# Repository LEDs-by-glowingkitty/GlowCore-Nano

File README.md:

# GlowCore-Nano
The tiniest GlowCore ever! With all the core features you need to make LEDs glow.

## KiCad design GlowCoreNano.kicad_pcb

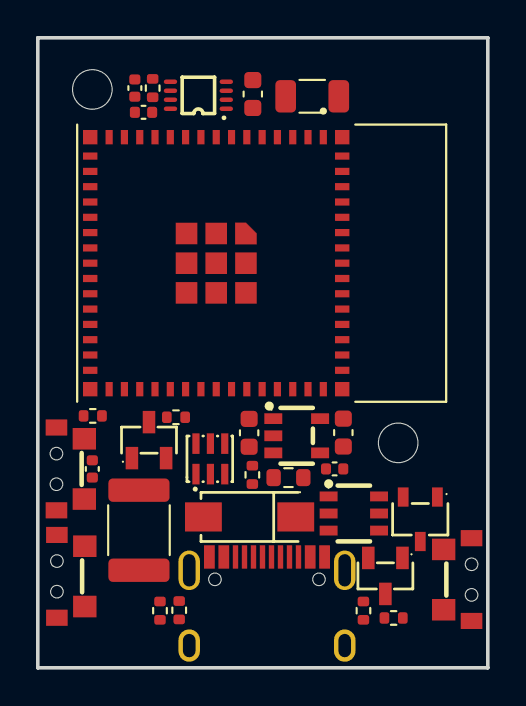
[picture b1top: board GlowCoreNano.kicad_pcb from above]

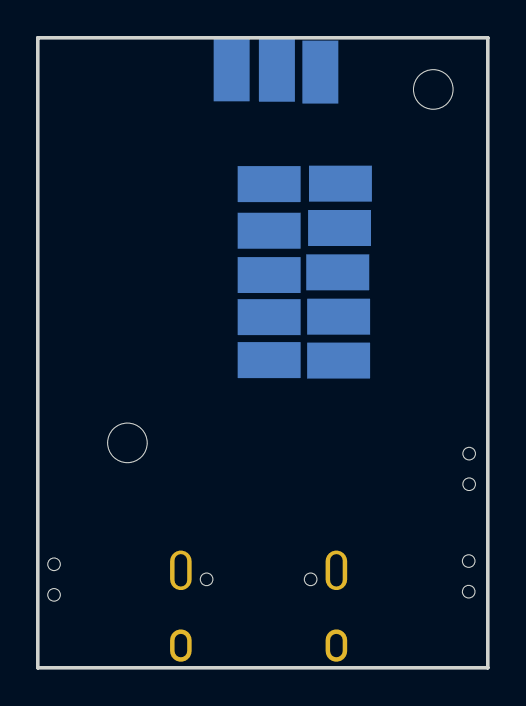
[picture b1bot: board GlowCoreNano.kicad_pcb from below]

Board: 2 copper layers, 25.0 x 35.0 mm, 46 parts (13 on the bottom side), 19 nets, no tracks yet.

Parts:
C1, C2: 0.1uF; C_0402_1005Metric
C3, C6, C14: 10uF; C_0603_1608Metric
C4: 1uF; C_0402_1005Metric
C5: 220uF; C_1206_3216Metric
C8: 10nF; C_0402_1005Metric
F1: BSMD1812-300-16V; Fuse_1812_4532Metric_Pad1.30x3.40mm_HandSolder
H1, H2: MountingHole_Pad; MountingHole_2.2mm_M2_ISO7380
P1, P2, P3, P4, P5, P6, P8, P9, P10, P11, P12, P13, P14: Solder_Pad; Solder pad
R1: 62; R_0402_1005Metric
R2, R7, R8: 5.1K; R_0402_1005Metric
R3, R5, R6, R9: 100K; R_0402_1005Metric
R4: 160K; R_0603_1608Metric
SW1, SW3, SW4: TS24CA; SW-SMD_TS24CA
U1: ESP32-S3-MINI-1-N8
U2: SN74LVC2T45DCUR; VSSOP-8_L2.4-W2.1-P0.50-LS3.2-BR
U3: SN74LVC1G373DBVR; SOT-23-6_L2.9-W1.6-P0.95-LS2.8-BR
U4, U5: AP40P05; SOT-23-3_L2.9-W1.3-P1.90-LS2.4-BR
U6: SPX3819M5-L-3-3_TR; SOT-23-5_L3.0-W1.7-P0.95-LS2.8-BR
U7: SS54; SMA_L4.4-W2.8-LS5.4-RD
U8: SK9822-EC20; LED-SMD_6P-L2.0-W2.0-P0.80-TL
U9: AO3400A; SOT-23-3_L2.9-W1.6-P1.90-LS2.8-BR
USB1: U262-161N-4BVC11; USB-3.1-SMD_U262-161N-4BVC11

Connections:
5V AFTER MOSFET: C1.1, C5.1, P1.1, U2.1 (VCCA), U4.3 (D), U8.5 (VDD)
+3V3: C2.1, C3.1, C14.2, P10.1, R2.1, R9.2, SW1.3, U2.8 (VCCB), U3.5 (VCC), U5.2 (S), U6.5 (OUT)
+5V: C6.2, P4.1, R5.2, U4.2 (S), U6.1 (IN), U6.3 (EN), U7.1 (K)
EN: C4.1, R2.2, SW3.4
GND: C1.2, C2.2, C3.2, C4.2, C5.2, C6.1, C8.1, C14.1, P3.1, P5.1, R4.1, R6.1, R7.1, R8.1, SW3.3, SW4.3, U2.3 (A2), U2.4 (GND), U2.5 (DIR), U2.6 (B2), U3.2 (GND), U6.2 (GND), U8.2 (GND), U9.2 (S), USB1.A1B12 (GND), USB1.B1A12 (GND), USB1.SHELL
IO25/VBUS: R3.1, R4.2
IO33/MAINBUTTON: P13.1, SW1.4
LED1 DATA OUT: P2.1, R1.2
unnamed: C8.2, U6.4 (BYP)
unnamed: F1.1, USB1.A4B9 (VBUS), USB1.B4A9 (VBUS)
unnamed: R1.1, U2.2 (A1)
unnamed: R5.1, R9.1, U4.1 (G), U5.1 (G), U9.3 (D)
unnamed: R6.2, U3.4 (Q), U9.1 (G)
unnamed: U1.1 (GND), U1.2 (GND), U1.42 (GND), U1.43 (GND), U1.46 (GND), U1.47 (GND), U1.48 (GND), U1.49 (GND), U1.50 (GND), U1.51 (GND), U1.52 (GND), U1.53 (GND), U1.54 (GND), U1.55 (GND), U1.56 (GND), U1.57 (GND), U1.58 (GND), U1.59 (GND), U1.60 (GND), U1.61 (GND), U1.61_1 (GND), U1.61_2 (GND), U1.61_3 (GND), U1.61_4 (GND), U1.61_5 (GND), U1.61_6 (GND), U1.61_7 (GND), U1.61_8 (GND), U1.62 (GND), U1.63 (GND), U1.64 (GND), U1.65 (GND)
USB-C CC1: R7.2, USB1.A5 (CC1)
USB-C CC2: R8.2, USB1.B5 (CC2)
USB-C DATA+: USB1.A6 (DP1), USB1.B6 (DP2)
USB-C DATA-: USB1.A7 (DN1), USB1.B7 (DN2)
VBUS: F1.2, R3.2, U7.2 (A)

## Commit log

2022-12-24 added first pcb design draft (in dev)
